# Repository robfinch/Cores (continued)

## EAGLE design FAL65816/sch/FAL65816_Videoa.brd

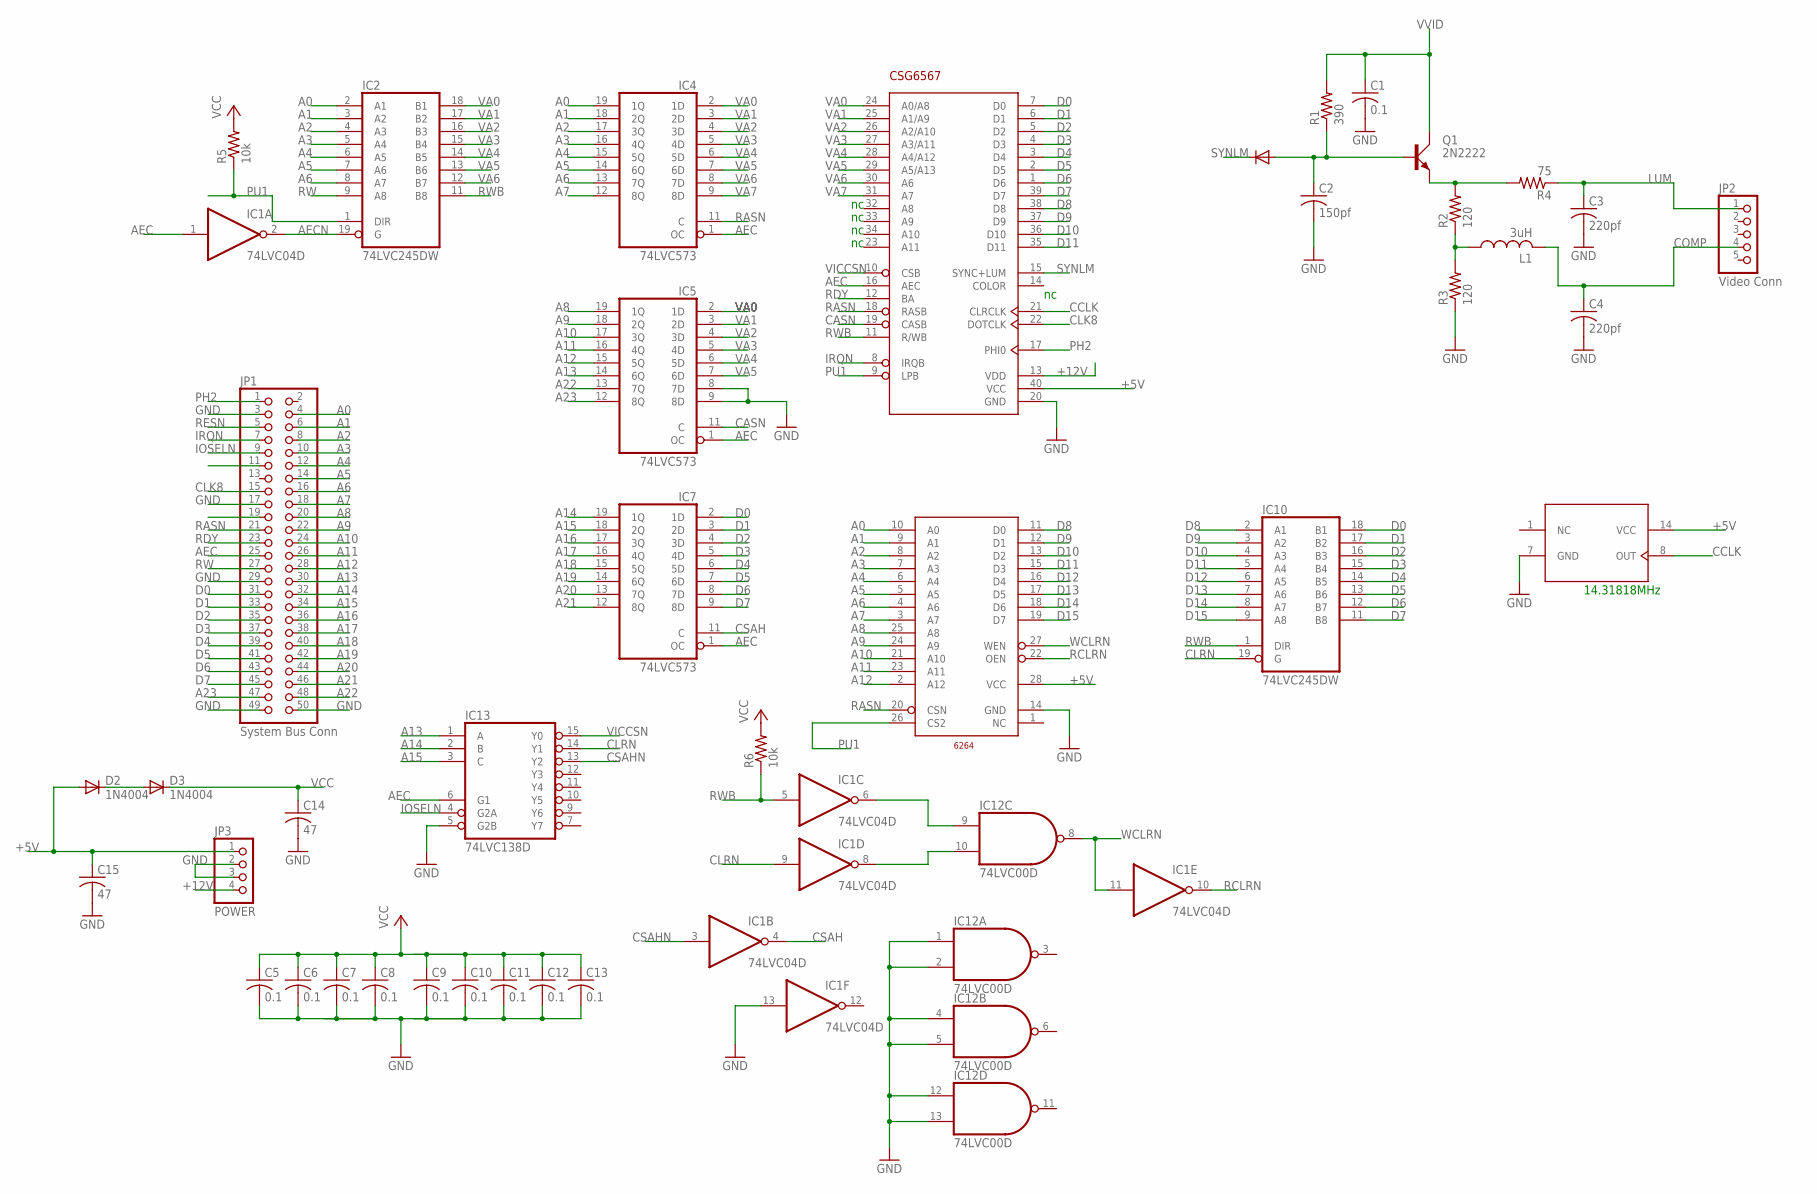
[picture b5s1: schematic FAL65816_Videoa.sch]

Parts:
C1, C5, C6, C7, C8, C9, C10, C11, C12, C13: 0.1; C050-024X044
C2: 150pf; C050-024X044
C3, C4: 220pf; C050-024X044
C14, C15: 47; C050-024X044
D2, D3: 1N4004; DO41-10
IC1: 74LVC04D; SO14
IC2, IC10: 74LVC245DW; SO20W
IC4, IC5, IC7: 74LVC573; SO20W
IC12: 74LVC00D; SO14
IC13: 74LVC138D; SO16
JP1: System Bus Conn; 2X25/90
JP2: Video Conn; 1X05
JP3: POWER; 1X04/90
L1: 3uH; 0204/7
Q1: 2N2222; TO18A
R1: 390; 0204/7
R2, R3: 120; 0204/7
R4: 75; 0204/7
R5, R6: 10k; 0204/7
U$1: CSG6567; DIP-40
U$3: OSC14; DIL14
U$4: 6264; DIL28-6

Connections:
+5V: C15.1, D2.A, JP3.1, U$1.40 (VCC), U$3.14 (VCC), U$4.28 (VCC)
+12V: JP3.4, U$1.13 (VDD)
A0: IC2.2 (A1), IC4.19 (1Q), JP1.4, U$4.10 (A0)
A1: IC2.3 (A2), IC4.18 (2Q), JP1.6, U$4.9 (A1)
A2: IC2.4 (A3), IC4.17 (3Q), JP1.8, U$4.8 (A2)
A3: IC2.5 (A4), IC4.16 (4Q), JP1.10, U$4.7 (A3)
A4: IC2.6 (A5), IC4.15 (5Q), JP1.12, U$4.6 (A4)
A5: IC2.7 (A6), IC4.14 (6Q), JP1.14, U$4.5 (A5)
A6: IC2.8 (A7), IC4.13 (7Q), JP1.16, U$4.4 (A6)
A7: IC4.12 (8Q), JP1.18, U$4.3 (A7)
A8: IC5.19 (1Q), JP1.20, U$4.25 (A8)
A9: IC5.18 (2Q), JP1.22, U$4.24 (A9)
A10: IC5.17 (3Q), JP1.24, U$4.21 (A10)
A11: IC5.16 (4Q), JP1.26, U$4.23 (A11)
A12: IC5.15 (5Q), JP1.28, U$4.2 (A12)
A13: IC5.14 (6Q), IC13.1 (A), JP1.30
A14: IC7.19 (1Q), IC13.2 (B), JP1.32
A15: IC7.18 (2Q), IC13.3 (C), JP1.34
A16: IC7.17 (3Q), JP1.36
A17: IC7.16 (4Q), JP1.38
A18: IC7.15 (5Q), JP1.40
A19: IC7.14 (6Q), JP1.42
A20: IC7.13 (7Q), JP1.44
A21: IC7.12 (8Q), JP1.46
A22: IC5.13 (7Q), JP1.48
A23: IC5.12 (8Q), JP1.47
AEC: IC1.1 (I), IC4.1 (OC), IC5.1 (OC), IC7.1 (OC), IC13.6 (G1), JP1.25, U$1.16 (AEC)
AECN: IC1.2 (O), IC2.19 (G)
CASN: IC5.11 (C), U$1.19 (CASB)
CCLK: U$1.21 (CLRCLK), U$3.8 (OUT)
CLK8: JP1.15, U$1.22 (DOTCLK)
CLRN: IC1.9 (I), IC10.19 (G), IC13.14 (Y1)
COMP: C4.1, JP2.4, L1.2
CSAH: IC1.4 (O), IC7.11 (C)
CSAHN: IC1.3 (I), IC13.13 (Y2)
D0: IC7.2 (1D), IC10.18 (B1), JP1.31, U$1.7 (D0)
D1: IC7.3 (2D), IC10.17 (B2), JP1.33, U$1.6 (D1)
D2: IC7.4 (3D), IC10.16 (B3), JP1.35, U$1.5 (D2)
D3: IC7.5 (4D), IC10.15 (B4), JP1.37, U$1.4 (D3)
D4: IC7.6 (5D), IC10.14 (B5), JP1.39, U$1.3 (D4)
D5: IC7.7 (6D), IC10.13 (B6), JP1.41, U$1.2 (D5)
D6: IC7.8 (7D), IC10.12 (B7), JP1.43, U$1.1 (D6)
D7: IC7.9 (8D), IC10.11 (B8), JP1.45, U$1.39 (D7)
D8: IC10.2 (A1), U$1.38 (D8), U$4.11 (D0)
D9: IC10.3 (A2), U$1.37 (D9), U$4.12 (D1)
D10: IC10.4 (A3), U$1.36 (D10), U$4.13 (D2)
D11: IC10.5 (A4), U$1.35 (D11), U$4.15 (D3)
D12: IC10.6 (A5), U$4.16 (D4)
D13: IC10.7 (A6), U$4.17 (D5)
D14: IC10.8 (A7), U$4.18 (D6)
D15: IC10.9 (A8), U$4.19 (D7)
GND: C1.2, C2.2, C3.2, C4.2, C5.2, C6.2, C7.2, C8.2, C9.2, C10.2, C11.2, C12.2, C13.2, C14.2, C15.2, IC1.7 (GND), IC1.13 (I), IC2.10 (GND), IC4.10 (GND), IC5.8 (7D), IC5.9 (8D), IC5.10 (GND), IC7.10 (GND), IC10.10 (GND), IC12.1 (I0), IC12.2 (I1), IC12.4 (I0), IC12.5 (I1), IC12.7 (GND), IC12.12 (I0), IC12.13 (I1), IC13.5 (G2B), IC13.8 (GND), JP1.3, JP1.17, JP1.29, JP1.49, JP1.50, JP3.2, JP3.3, R3.1, U$1.20 (GND), U$3.7 (GND), U$4.14 (GND)
IOSELN: IC13.4 (G2A), JP1.9
IRQN: JP1.7, U$1.8 (IRQB)
LUM: C3.1, JP2.1, R4.1
unnamed: D2.C, D3.A
unnamed: IC1.6 (O), IC12.9 (I0)
unnamed: IC1.8 (O), IC12.10 (I1)
unnamed: C2.1, Q1.B, R1.1
unnamed: L1.1, R2.1, R3.2
unnamed: Q1.E, R2.2, R4.2
PH2: JP1.1, U$1.17 (PHI0)
PU1: IC2.1 (DIR), R5.1, U$1.9 (LPB), U$4.26 (CS2)
RASN: IC4.11 (C), JP1.21, U$1.18 (RASB), U$4.20 (CSN)
RCLRN: IC1.10 (O), U$4.22 (OEN)
RDY: JP1.23, U$1.12 (BA)
RESN: JP1.5
RW: IC2.9 (A8), JP1.27
RWB: IC1.5 (I), IC2.11 (B8), IC10.1 (DIR), R6.1, U$1.11 (R/WB)
SYNLM: U$1.15 (SYNC+LUM)
VA0: IC2.18 (B1), IC4.2 (1D), IC5.2 (1D), U$1.24 (A0/A8)
VA1: IC2.17 (B2), IC4.3 (2D), IC5.3 (2D), U$1.25 (A1/A9)
VA2: IC2.16 (B3), IC4.4 (3D), IC5.4 (3D), U$1.26 (A2/A10)
VA3: IC2.15 (B4), IC4.5 (4D), IC5.5 (4D), U$1.27 (A3/A11)
VA4: IC2.14 (B5), IC4.6 (5D), IC5.6 (5D), U$1.28 (A4/A12)
VA5: IC2.13 (B6), IC4.7 (6D), IC5.7 (6D), U$1.29 (A5/A13)
VA6: IC2.12 (B7), IC4.8 (7D), U$1.30 (A6)
VA7: IC4.9 (8D), U$1.31 (A7)
VCC: C5.1, C6.1, C7.1, C8.1, C9.1, C10.1, C11.1, C12.1, C13.1, C14.1, D3.C, IC1.14 (VCC), IC2.20 (VCC), IC4.20 (VCC), IC5.20 (VCC), IC7.20 (VCC), IC10.20 (VCC), IC12.14 (VCC), IC13.16 (VCC), R5.2, R6.2
VICCSN: IC13.15 (Y0), U$1.10 (CSB)
VVID: C1.1, Q1.C, R1.2
WCLRN: IC1.11 (I), IC12.8 (O), U$4.27 (WEN)

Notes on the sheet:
14.31818MHz

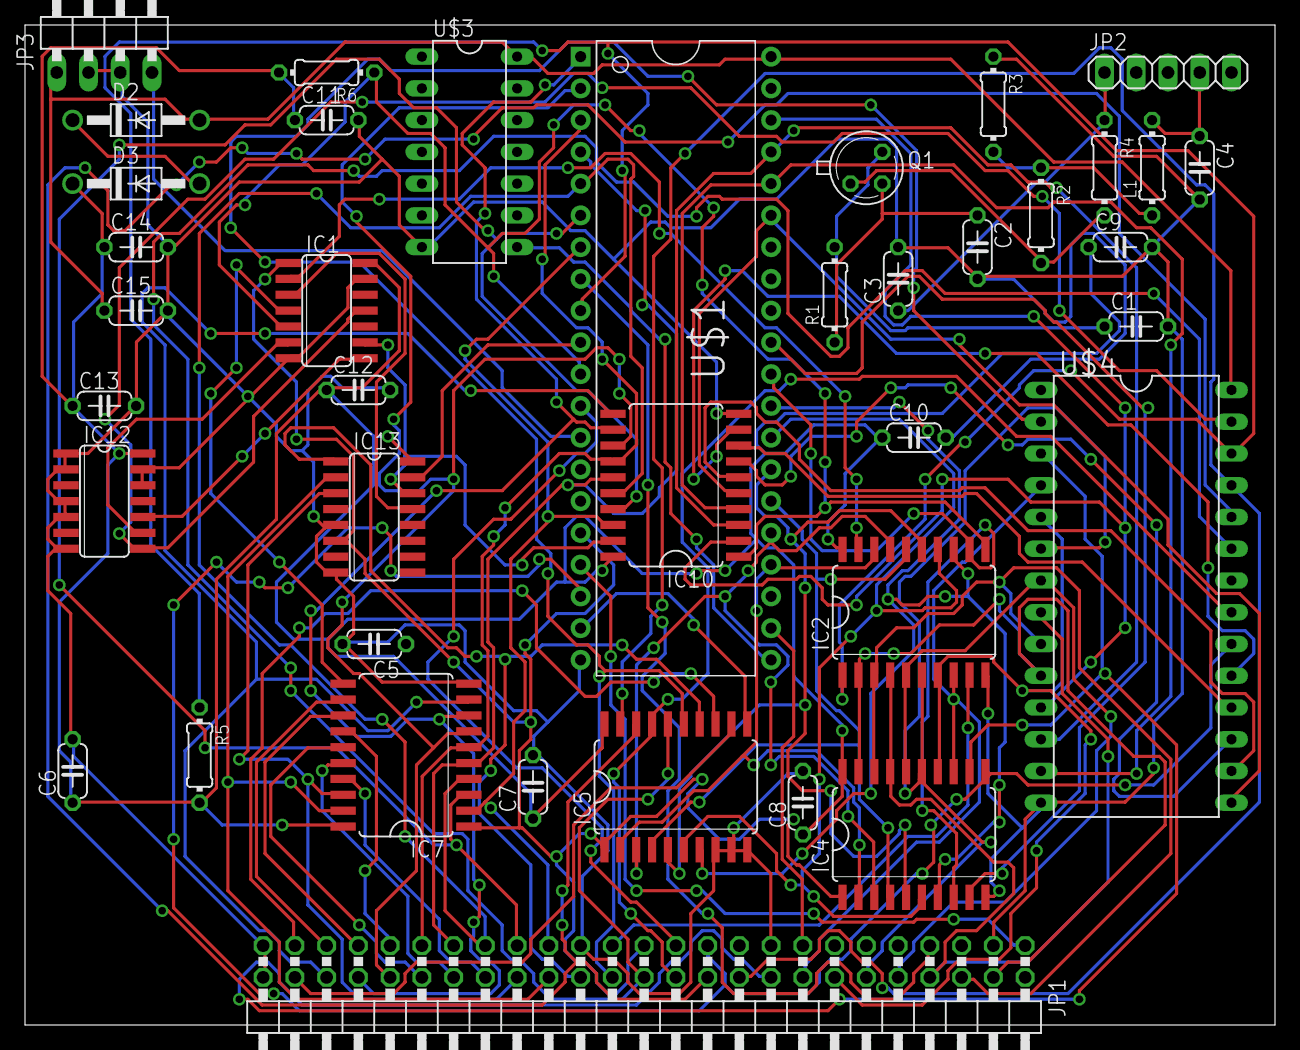
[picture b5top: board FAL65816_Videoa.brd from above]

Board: 2 copper layers, 100.0 x 80.0 mm, 39 parts (0 on the bottom side), 80 nets.

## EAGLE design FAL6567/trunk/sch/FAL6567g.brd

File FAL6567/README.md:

# FAL6567

This set of cores makes up a 6567 VIC-II compatible circuit. The core would be implmented in an FPGA or other PLD and would need additional logic for level translations to substitute into a 6567 socket.

## Features
HDMI output
16 sprites
80 column text mode

## Output
Most modern TV's and monitors support HDMI inputs.

## Sprites
By making use of fast paged mode, FPM, of the dynamic RAM, FAL6567 may support up to 16 sprites.
The additional sprites reuse the existing registers. There is a switch in register 32h which selects which sprite registers are visible.
Register 32h may be used to select legacy sprite operation and the set of sprite registers visible.
When 80 column text mode is active sprites may be positioned at only every other X pixel location. This is a design choice because there are 1040 horizontal positions in 80 column mode requiring 10 bits to represent, but the VIC-II register set has room for only a nine-bit coordinate.

## 80 Column Text
A modern display can easily display 80 columns of text in a crisp clean fashion without blurring or fuzziness.
Because the displayed image is rendered to an internal buffer to convert the image to DVI/HDMI output an 80 column mode is possible without needing to increase the frequency of memory access.
Twice as much memory is scanned for character data, this results in longer badlines.

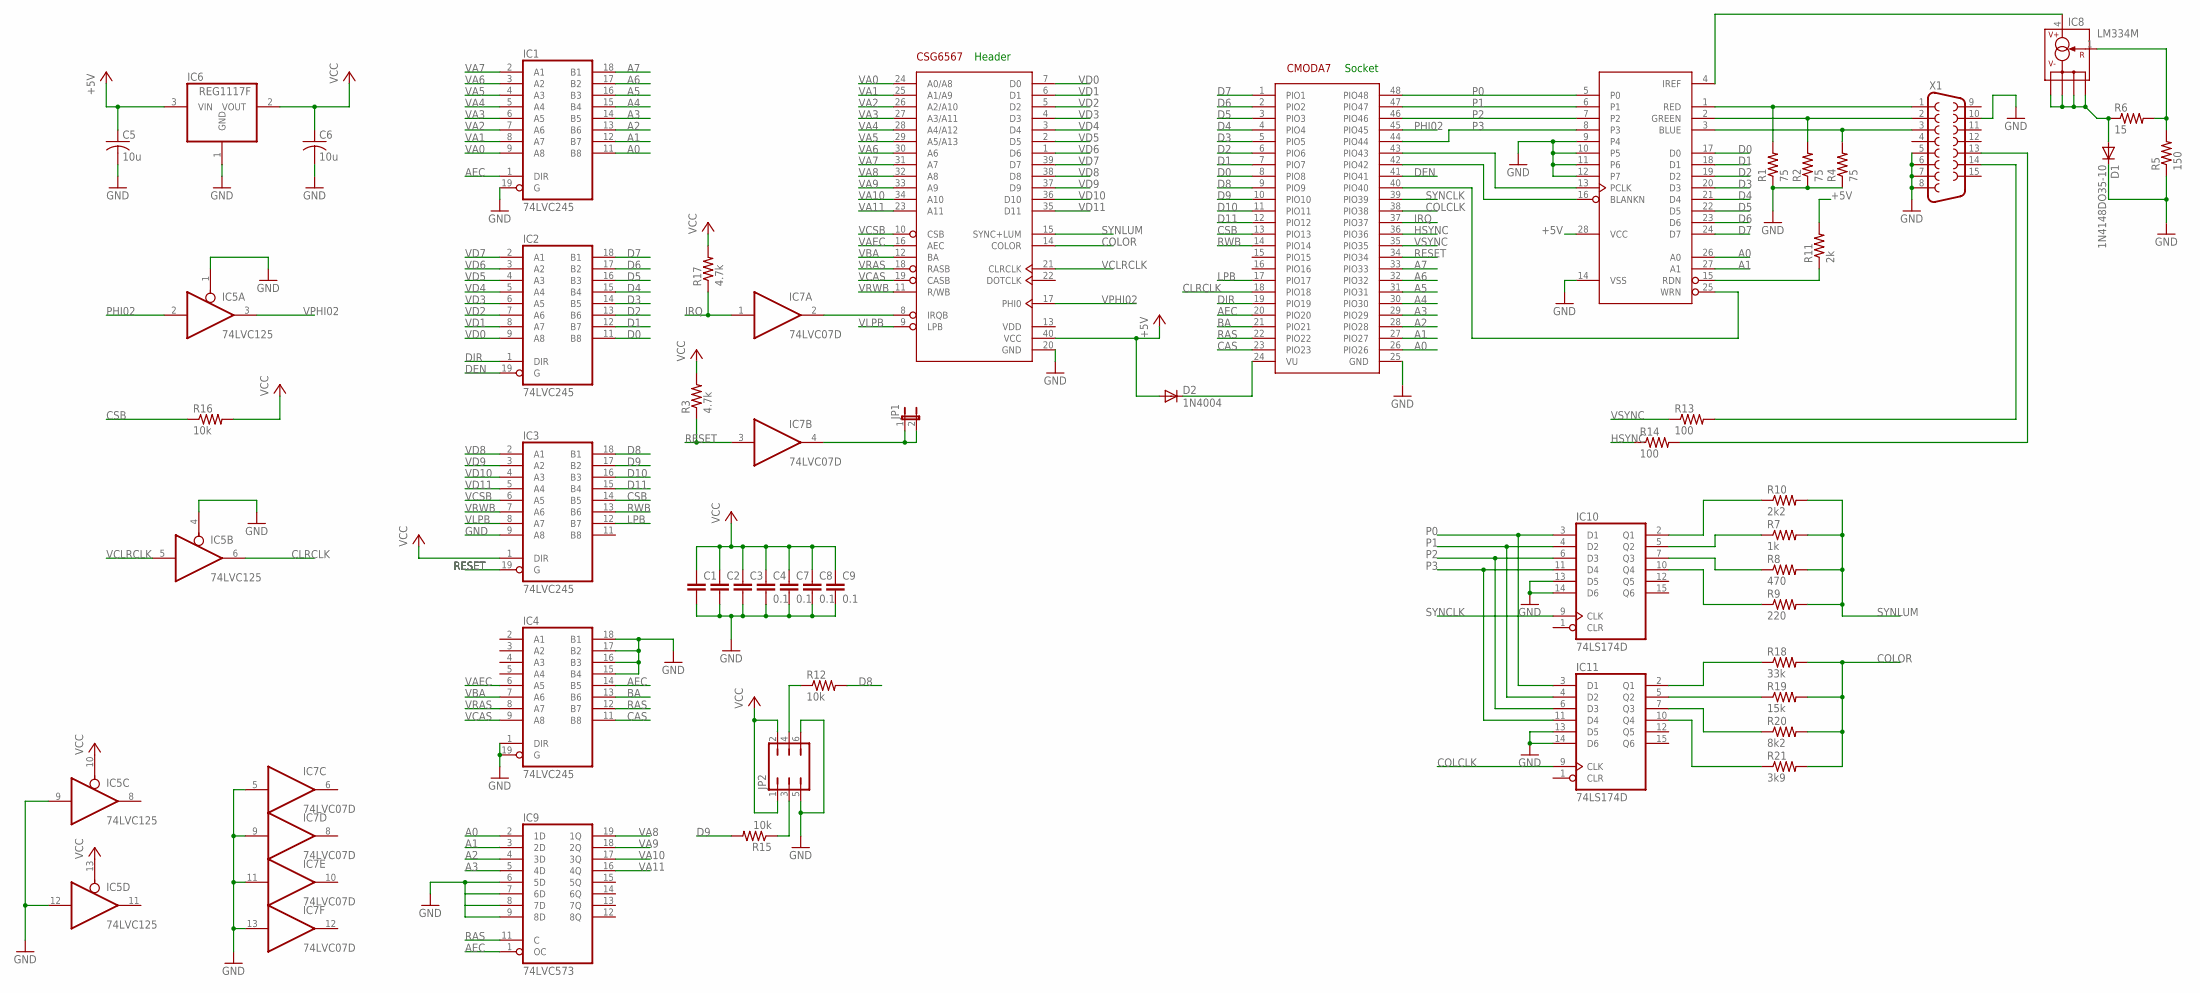
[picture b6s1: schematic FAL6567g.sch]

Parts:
C1, C2, C3: C-EU050-024X044; C050-024X044
C4, C7, C8, C9: 0.1; C050-024X044
C5, C6: 10u; C1206
D1: 1N4148DO35-10; DO35-10
D2: 1N4004; DO41-10
IC1, IC2, IC3, IC4: 74LVC245; SO20W
IC5: 74LVC125; SO14
IC6: REG1117F; DD-3
IC7: 74LVC07D; SO14
IC8: LM334M; SO08
IC9: 74LVC573; SO20W
IC10, IC11: 74LS174D; SO16
JP1: JP1E; JP1
JP2: JP3Q
R1, R2, R4: 75; 0204/7
R3, R17: 4.7k; 0204/7
R5: 150; 0204/7
R6: 15; 0204/7
R7: 1k; 0204/7
R8: 470; 0204/7
R9: 220; 0204/7
R10: 2k2; 0204/7
R11: 2k; 0204/7
R12, R15, R16: 10k; 0204/7
R13, R14: 100; 0204/7
R18: 33k; 0204/7
R19: 15k; 0204/7
R20: 8k2; 0204/7
R21: 3k9; 0204/7
U$1: CSG6567; DIP-40
U$2: CMODA7; DIL48
U$3: ADV476; DIL28-6
X1: F15HDV; HDF15V

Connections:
+5V: C5.1, D2.A, IC6.3 (VIN), R11.2, U$1.40 (VCC), U$3.28 (VCC)
A0: IC1.11 (B8), IC9.2 (1D), U$2.26 (PIO26), U$3.26 (A0)
A1: IC1.12 (B7), IC9.3 (2D), U$2.27 (PIO27), U$3.27 (A1)
A2: IC1.13 (B6), IC9.4 (3D), U$2.28 (PIO28)
A3: IC1.14 (B5), IC9.5 (4D), U$2.29 (PIO29)
A4: IC1.15 (B4), U$2.30 (PIO30)
A5: IC1.16 (B3), U$2.31 (PIO31)
A6: IC1.17 (B2), U$2.32 (PIO32)
A7: IC1.18 (B1), U$2.33 (PIO33)
AEC: IC1.1 (DIR), IC4.14 (B5), IC9.1 (OC), U$2.20 (PIO20)
BA: IC4.13 (B6), U$2.21 (PIO21)
CAS: IC4.11 (B8), U$2.23 (PIO23)
CLRCLK: IC5.6 (O), U$2.18 (PIO18)
COLCLK: IC11.9 (CLK), U$2.38 (PIO38)
COLOR: R18.2, R19.2, R20.2, R21.2, U$1.14 (COLOR)
CSB: IC3.14 (B5), R16.1, U$2.13 (PIO13)
D0: IC2.11 (B8), U$2.8 (PIO8), U$3.17 (D0)
D1: IC2.12 (B7), U$2.7 (PIO7), U$3.18 (D1)
D2: IC2.13 (B6), U$2.6 (PIO6), U$3.19 (D2)
D3: IC2.14 (B5), U$2.5 (PIO5), U$3.20 (D3)
D4: IC2.15 (B4), U$2.4 (PIO4), U$3.21 (D4)
D5: IC2.16 (B3), U$2.3 (PIO3), U$3.22 (D5)
D6: IC2.17 (B2), U$2.2 (PIO2), U$3.23 (D6)
D7: IC2.18 (B1), U$2.1 (PIO1), U$3.24 (D7)
D8: IC3.18 (B1), R12.2, U$2.9 (PIO9)
D9: IC3.17 (B2), R15.2, U$2.10 (PIO10)
D10: IC3.16 (B3), U$2.11 (PIO11)
D11: IC3.15 (B4), U$2.12 (PIO12)
DEN: IC2.19 (G), U$2.41 (PIO41)
DIR: IC2.1 (DIR), U$2.19 (PIO19)
GND: C1.2, C2.2, C3.2, C4.2, C5.2, C6.2, C7.2, C8.2, C9.2, D1.C, IC1.10 (GND), IC1.19 (G), IC2.10 (GND), IC3.9 (A8), IC3.10 (GND), IC4.1 (DIR), IC4.10 (GND), IC4.15 (B4), IC4.16 (B3), IC4.17 (B2), IC4.18 (B1), IC4.19 (G), IC5.1 (OE), IC5.4 (OE), IC5.7 (GND), IC5.9 (I), IC5.12 (I), IC6.1 (GND), IC7.5 (I), IC7.7 (GND), IC7.9 (I), IC7.11 (I), IC7.13 (I), IC9.6 (5D), IC9.9 (8D), IC9.10 (GND), IC10.8 (GND), IC10.13 (D5), IC10.14 (D6), IC11.8 (GND), IC11.13 (D5), IC11.14 (D6), JP2.5, JP2.6, R1.1, R2.1, R4.1, R5.1, U$1.20 (GND), U$2.25 (GND), U$3.9 (P4), U$3.10 (P5), U$3.11 (P6), U$3.12 (P7), U$3.14 (VSS), X1.5, X1.6, X1.7, X1.8, X1.10
HSYNC: R14.1, U$2.36 (PIO36)
IRQ: IC7.1 (I), R17.1, U$2.37 (PIO37)
LPB: IC3.12 (B7), U$2.17 (PIO17)
MD0: JP2.4, R12.1
MD1: JP2.3, R15.1
unnamed: IC7.2 (O), U$1.8 (IRQB)
unnamed: IC10.2 (Q1), R10.1
unnamed: D2.C, U$2.24 (VU)
unnamed: IC10.5 (Q2), R7.1
unnamed: R1.2, U$3.1 (RED), X1.1
unnamed: IC7.4 (O), JP1.1, JP1.2
unnamed: IC10.7 (Q3), R8.1
unnamed: R2.2, U$3.2 (GREEN), X1.2
unnamed: IC10.10 (Q4), R9.1
unnamed: R14.2, X1.13
unnamed: R13.2, X1.14
unnamed: U$2.40 (PIO40), U$3.25 (WRN)
unnamed: R4.2, U$3.3 (BLUE), X1.3
unnamed: IC8.1 (R), R5.2, R6.2
unnamed: IC11.2 (Q1), R18.1
unnamed: IC11.5 (Q2), R19.1
unnamed: D1.A, IC8.2 (V-), IC8.3 (V-), IC8.6 (V-), IC8.7 (V-), R6.1
unnamed: IC8.4 (V+), U$3.4 (IREF)
unnamed: IC11.7 (Q3), R20.1
unnamed: U$2.43 (PIO43), U$3.13 (PCLK)
unnamed: U$2.42 (PIO42), U$3.16 (BLANKN)
unnamed: IC11.10 (Q4), R21.1
unnamed: R11.1, U$3.15 (RDN)
P0: IC10.3 (D1), IC11.3 (D1), U$2.48 (PIO48), U$3.5 (P0)
P1: IC10.4 (D2), IC11.4 (D2), U$2.47 (PIO47), U$3.6 (P1)
P2: IC10.6 (D3), IC11.6 (D3), U$2.46 (PIO46), U$3.7 (P2)
P3: IC10.11 (D4), IC11.11 (D4), U$2.44 (PIO44), U$3.8 (P3)
PHI02: IC5.2 (I), U$2.45 (PIO45)
RAS: IC4.12 (B7), IC9.11 (C), U$2.22 (PIO22)
RESET: IC3.19 (G), IC7.3 (I), R3.1, U$2.34 (PIO34)
RWB: IC3.13 (B6), U$2.14 (PIO14)
SYNCLK: IC10.9 (CLK), U$2.39 (PIO39)
SYNLUM: R7.2, R8.2, R9.2, R10.2, U$1.15 (SYNC+LUM)
VA0: IC1.9 (A8), U$1.24 (A0/A8)
VA1: IC1.8 (A7), U$1.25 (A1/A9)
VA2: IC1.7 (A6), U$1.26 (A2/A10)
VA3: IC1.6 (A5), U$1.27 (A3/A11)
VA4: IC1.5 (A4), U$1.28 (A4/A12)
VA5: IC1.4 (A3), U$1.29 (A5/A13)
VA6: IC1.3 (A2), U$1.30 (A6)
VA7: IC1.2 (A1), U$1.31 (A7)
VA8: IC9.19 (1Q), U$1.32 (A8)
VA9: IC9.18 (2Q), U$1.33 (A9)
VA10: IC9.17 (3Q), U$1.34 (A10)
VA11: IC9.16 (4Q), U$1.23 (A11)
VAEC: IC4.6 (A5), U$1.16 (AEC)
VBA: IC4.7 (A6), U$1.12 (BA)
VCAS: IC4.9 (A8), U$1.19 (CASB)
VCC: C1.1, C2.1, C3.1, C4.1, C6.1, C7.1, C8.1, C9.1, IC1.20 (VCC), IC2.20 (VCC), IC3.1 (DIR), IC3.20 (VCC), IC4.20 (VCC), IC5.10 (OE), IC5.13 (OE), IC5.14 (VCC), IC6.2 (VOUT), IC7.14 (VCC), IC9.20 (VCC), IC10.16 (VCC), IC11.16 (VCC), JP2.1, JP2.2, R3.2, R16.2, R17.2
VCLRCLK: IC5.5 (I), U$1.21 (CLRCLK)
VCSB: IC3.6 (A5), U$1.10 (CSB)
VD0: IC2.9 (A8), U$1.7 (D0)
VD1: IC2.8 (A7), U$1.6 (D1)
VD2: IC2.7 (A6), U$1.5 (D2)
VD3: IC2.6 (A5), U$1.4 (D3)
VD4: IC2.5 (A4), U$1.3 (D4)
VD5: IC2.4 (A3), U$1.2 (D5)
VD6: IC2.3 (A2), U$1.1 (D6)
VD7: IC2.2 (A1), U$1.39 (D7)
VD8: IC3.2 (A1), U$1.38 (D8)
VD9: IC3.3 (A2), U$1.37 (D9)
VD10: IC3.4 (A3), U$1.36 (D10)
VD11: IC3.5 (A4), U$1.35 (D11)
VDD: U$1.13 (VDD)
VLPB: IC3.8 (A7), U$1.9 (LPB)
VPHI02: IC5.3 (O), U$1.17 (PHI0)
VRAS: IC4.8 (A7), U$1.18 (RASB)
VRWB: IC3.7 (A6), U$1.11 (R/WB)
VSYNC: R13.1, U$2.35 (PIO35)

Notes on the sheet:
Header
Socket

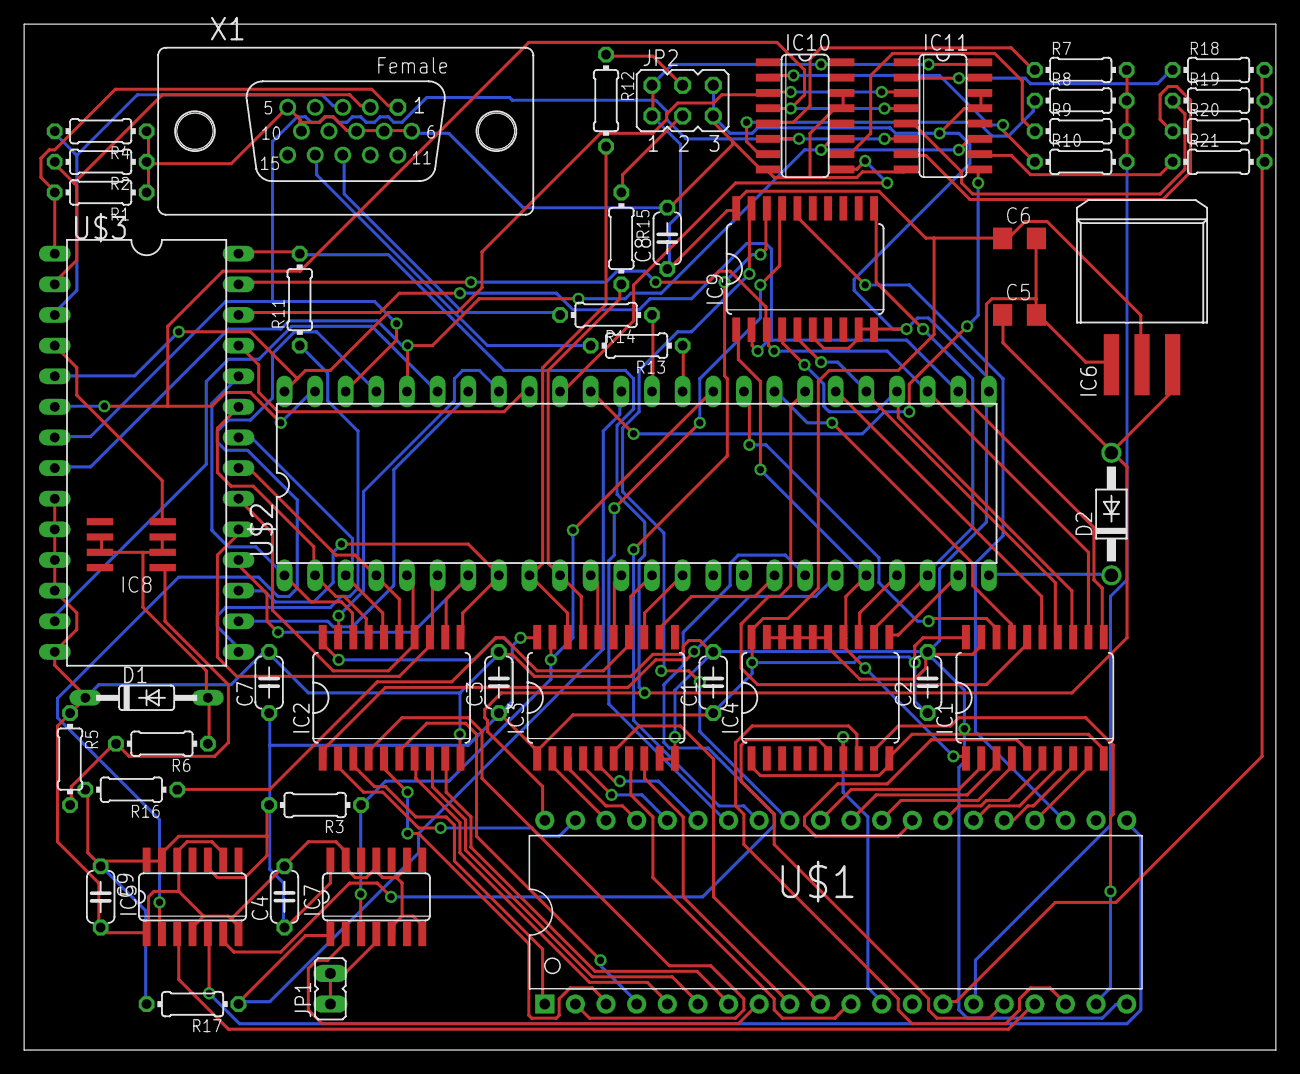
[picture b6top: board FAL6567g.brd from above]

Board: 2 copper layers, 103.8 x 85.1 mm, 50 parts (0 on the bottom side), 104 nets.

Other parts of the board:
DRILEGEND: DRILEGEND

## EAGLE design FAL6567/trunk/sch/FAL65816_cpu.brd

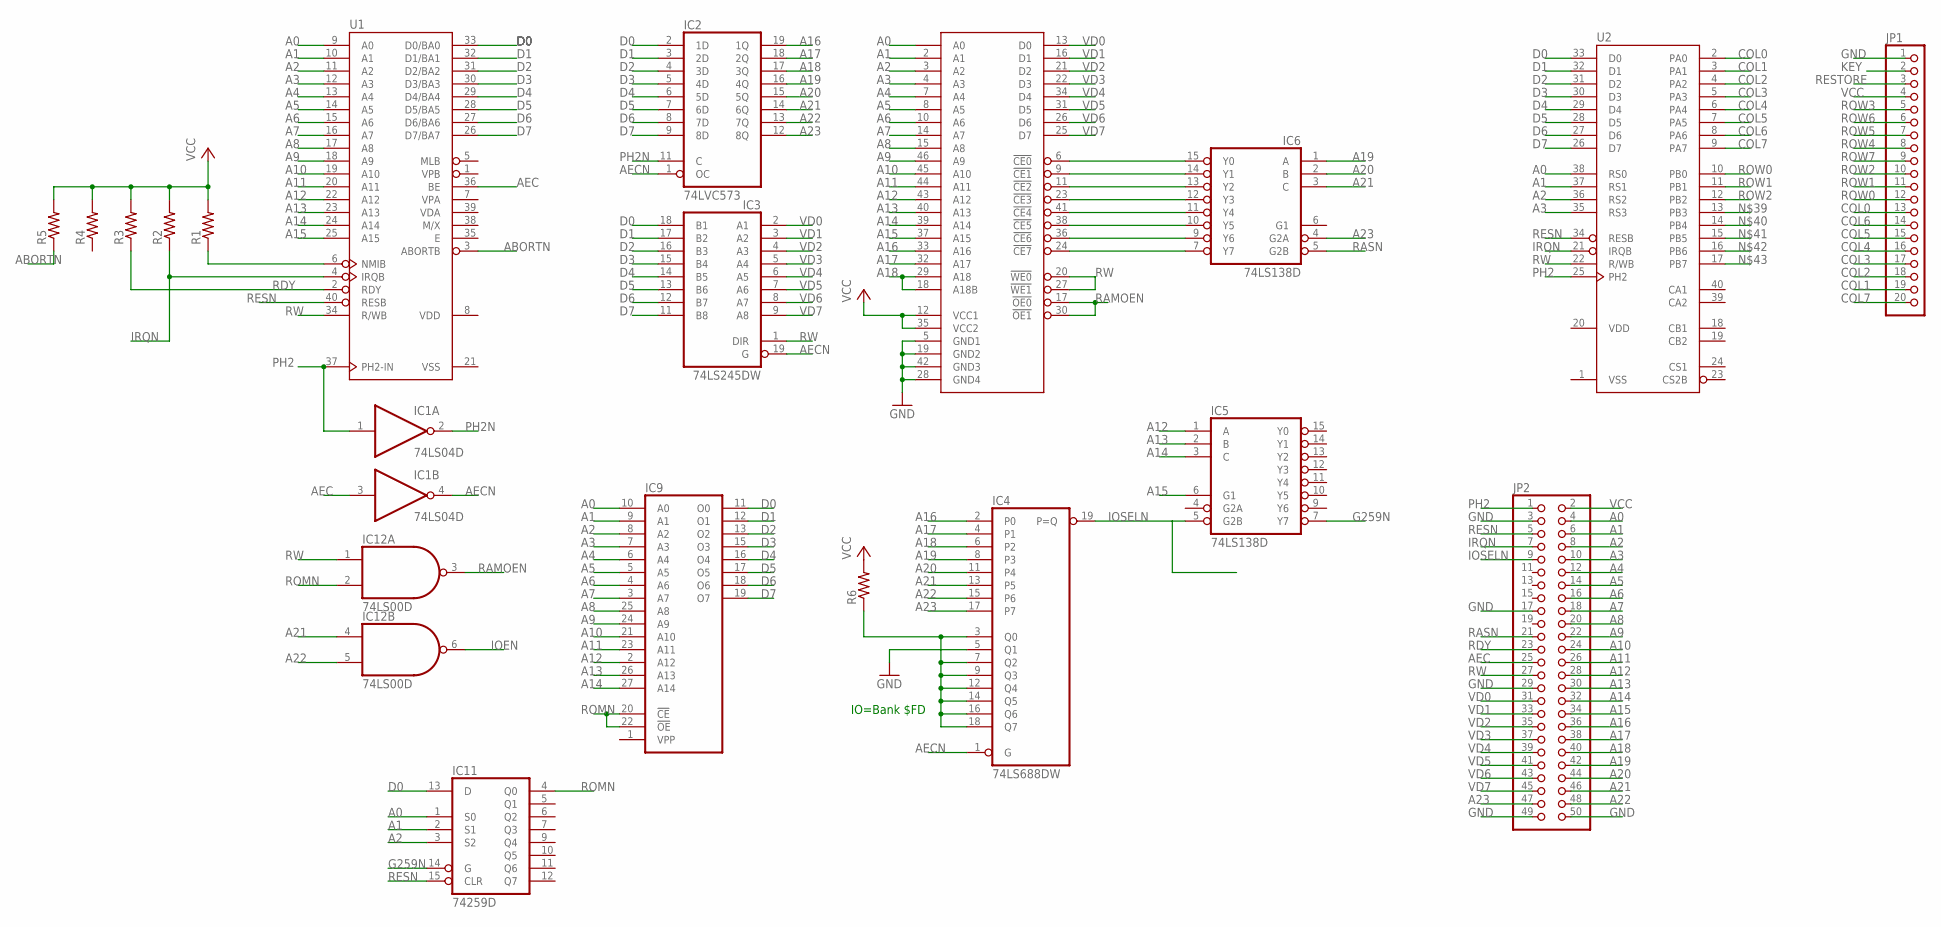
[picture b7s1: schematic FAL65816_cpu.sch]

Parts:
IC1: 74LS04D; SO14
IC2: 74LVC573; SO20W
IC3: 74LS245DW; SO20W
IC4: 74LS688DW; SO20W
IC5, IC6: 74LS138D; SO16
IC9: 27256; DIL28
IC11: 74259D; SO16
IC12: 74LS00D; SO14
JP1: PINHD-1X20; 1X20
JP2: PINHD-2X25; 2X25
R1, R2, R3, R4, R5: R-US_0207/10; 0207/10
R6: R-US_0204/7; 0204/7
U1: W65C816SP; DIP-40
U2: G65SC22P; DIP-40
U$2: WM-1RAM; DIL46-1

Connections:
A0: IC9.10 (A0), IC11.1 (S0), JP2.4, U1.9 (A0), U2.38 (RS0), U$2.1 (A0)
A1: IC9.9 (A1), IC11.2 (S1), JP2.6, U1.10 (A1), U2.37 (RS1), U$2.2 (A1)
A2: IC9.8 (A2), IC11.3 (S2), JP2.8, U1.11 (A2), U2.36 (RS2), U$2.3 (A2)
A3: IC9.7 (A3), JP2.10, U1.12 (A3), U2.35 (RS3), U$2.4 (A3)
A4: IC9.6 (A4), JP2.12, U1.13 (A4), U$2.7 (A4)
A5: IC9.5 (A5), JP2.14, U1.14 (A5), U$2.8 (A5)
A6: IC9.4 (A6), JP2.16, U1.15 (A6), U$2.10 (A6)
A7: IC9.3 (A7), JP2.18, U1.16 (A7), U$2.14 (A7)
A8: IC9.25 (A8), JP2.20, U1.17 (A8), U$2.15 (A8)
A9: IC9.24 (A9), JP2.22, U1.18 (A9), U$2.46 (A9)
A10: IC9.21 (A10), JP2.24, U1.19 (A10), U$2.45 (A10)
A11: IC9.23 (A11), JP2.26, U1.20 (A11), U$2.44 (A11)
A12: IC5.1 (A), IC9.2 (A12), JP2.28, U1.22 (A12), U$2.43 (A12)
A13: IC5.2 (B), IC9.26 (A13), JP2.30, U1.23 (A13), U$2.40 (A13)
A14: IC5.3 (C), IC9.27 (A14), JP2.32, U1.24 (A14), U$2.39 (A14)
A15: IC5.6 (G1), JP2.34, U1.25 (A15), U$2.37 (A15)
A16: IC2.19 (1Q), IC4.2 (P0), JP2.36, U$2.33 (A16)
A17: IC2.18 (2Q), IC4.4 (P1), JP2.38, U$2.32 (A17)
A18: IC2.17 (3Q), IC4.6 (P2), JP2.40, U$2.18 (A18B), U$2.29 (A18)
A19: IC2.16 (4Q), IC4.8 (P3), IC6.1 (A), JP2.42
A20: IC2.15 (5Q), IC4.11 (P4), IC6.2 (B), JP2.44
A21: IC2.14 (6Q), IC4.13 (P5), IC6.3 (C), IC12.4 (I0), JP2.46
A22: IC2.13 (7Q), IC4.15 (P6), IC12.5 (I1), JP2.48
A23: IC2.12 (8Q), IC4.17 (P7), IC6.4 (G2A), JP2.47
ABORTN: R5.1, U1.3 (ABORTB)
AEC: IC1.3 (I), JP2.25, U1.36 (BE)
AECN: IC1.4 (O), IC2.1 (OC), IC3.19 (G), IC4.1 (G)
COL0: JP1.13, U2.2 (PA0)
COL1: JP1.19, U2.3 (PA1)
COL2: JP1.18, U2.4 (PA2)
COL3: JP1.17, U2.5 (PA3)
COL4: JP1.16, U2.6 (PA4)
COL5: JP1.15, U2.7 (PA5)
COL6: JP1.14, U2.8 (PA6)
COL7: JP1.20, U2.9 (PA7)
D0: IC2.2 (1D), IC3.18 (B1), IC9.11 (O0), IC11.13 (D), U1.33 (D0/BA0), U2.33 (D0)
D1: IC2.3 (2D), IC3.17 (B2), IC9.12 (O1), U1.32 (D1/BA1), U2.32 (D1)
D2: IC2.4 (3D), IC3.16 (B3), IC9.13 (O2), U1.31 (D2/BA2), U2.31 (D2)
D3: IC2.5 (4D), IC3.15 (B4), IC9.15 (O3), U1.30 (D3/BA3), U2.30 (D3)
D4: IC2.6 (5D), IC3.14 (B5), IC9.16 (O4), U1.29 (D4/BA4), U2.29 (D4)
D5: IC2.7 (6D), IC3.13 (B6), IC9.17 (O5), U1.28 (D5/BA5), U2.28 (D5)
D6: IC2.8 (7D), IC3.12 (B7), IC9.18 (O6), U1.27 (D6/BA6), U2.27 (D6)
D7: IC2.9 (8D), IC3.11 (B8), IC9.19 (O7), U1.26 (D7/BA7), U2.26 (D7)
G259N: IC5.7 (Y7), IC11.14 (G)
GND: IC1.7 (GND), IC2.10 (GND), IC3.10 (GND), IC4.5 (Q1), IC4.10 (GND), IC5.8 (GND), IC6.8 (GND), IC9.14 (GND), IC11.8 (GND), IC12.7 (GND), JP1.1, JP2.3, JP2.17, JP2.29, JP2.49, JP2.50, U$2.5 (GND1), U$2.19 (GND2), U$2.28 (GND4), U$2.42 (GND3)
IOEN: IC12.6 (O)
IOSELN: IC4.19 (P=Q), IC5.5 (G2B), JP2.9
IRQN: JP2.7, R2.1, U1.4 (IRQB), U2.21 (IRQB)
KEY: JP1.2
unnamed: R1.1, U1.6 (NMIB)
unnamed: IC6.15 (Y0), U$2.6 (!CE0)
unnamed: IC6.14 (Y1), U$2.9 (!CE1)
unnamed: IC6.13 (Y2), U$2.11 (!CE2)
unnamed: IC6.12 (Y3), U$2.23 (!CE3)
unnamed: IC6.11 (Y4), U$2.41 (!CE4)
unnamed: IC6.10 (Y5), U$2.38 (!CE5)
unnamed: IC6.9 (Y6), U$2.36 (!CE6)
unnamed: IC6.7 (Y7), U$2.24 (!CE7)
unnamed: IC4.3 (Q0), IC4.7 (Q2), IC4.9 (Q3), IC4.12 (Q4), IC4.14 (Q5), IC4.16 (Q6), IC4.18 (Q7), R6.1
PH2: IC1.1 (I), JP2.1, U1.37 (PH2-IN), U2.25 (PH2)
PH2N: IC1.2 (O), IC2.11 (C)
RAMOEN: IC12.3 (O), U$2.17 (!OE0), U$2.30 (!OE1)
RASN: IC6.5 (G2B), JP2.21
RDY: JP2.23, R3.1, U1.2 (RDY)
RESN: IC11.15 (CLR), JP2.5, U1.40 (RESB), U2.34 (RESB)
RESTORE: JP1.3
ROMN: IC9.20 (!CE), IC9.22 (!OE), IC11.4 (Q0), IC12.2 (I1)
ROW0: JP1.12, U2.10 (PB0)
ROW1: JP1.11, U2.11 (PB1)
ROW2: JP1.10, U2.12 (PB2)
ROW3: JP1.5
ROW4: JP1.8
ROW5: JP1.7
ROW6: JP1.6
ROW7: JP1.9
RW: IC3.1 (DIR), IC12.1 (I0), JP2.27, U1.34 (R/WB), U2.22 (R/WB), U$2.20 (!WE0), U$2.27 (!WE1)
VCC: IC1.14 (VCC), IC2.20 (VCC), IC3.20 (VCC), IC4.20 (VCC), IC5.16 (VCC), IC6.16 (VCC), IC9.28 (VCC), IC11.16 (VCC), IC12.14 (VCC), JP1.4, JP2.2, R1.2, R2.2, R3.2, R4.2, R5.2, R6.2, U$2.12 (VCC1), U$2.35 (VCC2)
VD0: IC3.2 (A1), JP2.31, U$2.13 (D0)
VD1: IC3.3 (A2), JP2.33, U$2.16 (D1)
VD2: IC3.4 (A3), JP2.35, U$2.21 (D2)
VD3: IC3.5 (A4), JP2.37, U$2.22 (D3)
VD4: IC3.6 (A5), JP2.39, U$2.34 (D4)
VD5: IC3.7 (A6), JP2.41, U$2.31 (D5)
VD6: IC3.8 (A7), JP2.43, U$2.26 (D6)
VD7: IC3.9 (A8), JP2.45, U$2.25 (D7)
VDD: U1.8 (VDD), U2.20 (VDD)

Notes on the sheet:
IO=Bank $FD

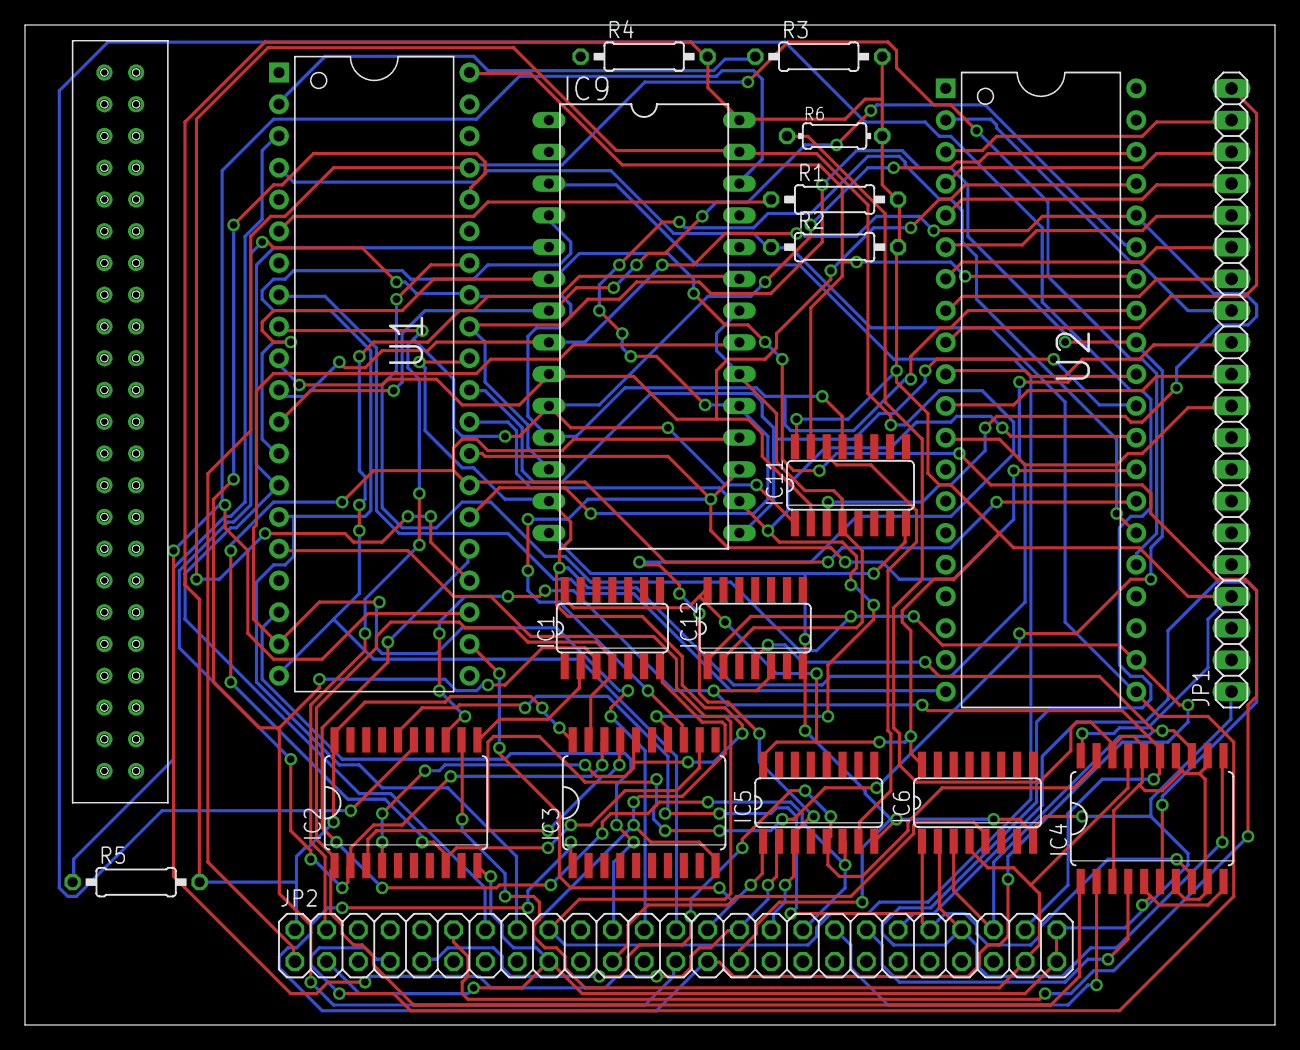
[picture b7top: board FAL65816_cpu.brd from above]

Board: 2 copper layers, 100.0 x 80.0 mm, 20 parts (0 on the bottom side), 78 nets.

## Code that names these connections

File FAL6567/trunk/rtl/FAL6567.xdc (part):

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#set_property -dict { PACKAGE_PIN M1    IOSTANDARD LVCMOS33 } [get_ports { pio2[0] }]; #IO_L9N_T1_DQS_AD7N_35 Sch=pio[17]
#set_property -dict { PACKAGE_PIN N3    IOSTANDARD LVCMOS33 } [get_ports { pio2[1] }]; #IO_L12P_T1_MRCC_35 Sch=pio[18]
set_property -dict { PACKAGE_PIN P3    IOSTANDARD LVCMOS33 } [get_ports { dir }]; #IO_L12N_T1_MRCC_35 Sch=pio[19]
set_property -dict { PACKAGE_PIN M2    IOSTANDARD LVCMOS33 } [get_ports { aec }]; #IO_L9P_T1_DQS_AD7P_35 Sch=pio[20]
set_property -dict { PACKAGE_PIN N1    IOSTANDARD LVCMOS33 } [get_ports { ba }]; #IO_L10N_T1_AD15N_35 Sch=pio[21]
set_property -dict { PACKAGE_PIN N2    IOSTANDARD LVCMOS33 } [get_ports { ras_n }]; #IO_L10P_T1_AD15P_35 Sch=pio[22]
set_property -dict { PACKAGE_PIN P1    IOSTANDARD LVCMOS33 } [get_ports { cas_n }]; #IO_L19N_T3_VREF_35 Sch=pio[23]
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set_property -dict { PACKAGE_PIN V2    IOSTANDARD TMDS_33 } [get_ports { TMDS_OUT_data_p[2] }]; #IO_L5P_T0_34 Sch=pio[33]
set_property -dict { PACKAGE_PIN W2    IOSTANDARD TMDS_33 } [get_ports { TMDS_OUT_data_n[2] }]; #IO_L5N_T0_34 Sch=pio[32]
set_property -dict { PACKAGE_PIN W3    IOSTANDARD LVCMOS33 } [get_ports { RESET }]; #IO_L6N_T0_VREF_34 Sch=pio[34]
set_property -dict { PACKAGE_PIN V3    IOSTANDARD LVCMOS33 } [get_ports { phi02 }]; #IO_L6P_T0_34 Sch=pio[35]
#set_property -dict { PACKAGE_PIN W5    IOSTANDARD LVCMOS33 } [get_ports { pio3[10] }]; #IO_L12P_T1_MRCC_34 Sch=pio[36]
set_property -dict { PACKAGE_PIN V4    IOSTANDARD LVCMOS33 } [get_ports { irq }]; #IO_L11N_T1_SRCC_34 Sch=pio[37]
#set_property -dict { PACKAGE_PIN U4    IOSTANDARD LVCMOS33 } [get_ports { pio3[12] }]; #IO_L11P_T1_SRCC_34 Sch=pio[38]
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#set_property -dict { PACKAGE_PIN V13   IOSTANDARD LVCMOS33 } [get_ports { MemDB[5]   }]; #IO_L24P_T3_A01_D17_14 Sch=sram-dq[5]
#set_property -dict { PACKAGE_PIN V14   IOSTANDARD LVCMOS33 } [get_ports { MemDB[6]   }]; #IO_L24N_T3_A00_D16_14 Sch=sram-dq[6]
#set_property -dict { PACKAGE_PIN U14   IOSTANDARD LVCMOS33 } [get_ports { MemDB[7]   }]; #IO_25_14 Sch=sram-dq[7]
#set_property -dict { PACKAGE_PIN P19   IOSTANDARD LVCMOS33 } [get_ports { RamOEn     }]; #IO_L10P_T1_D14_14 Sch=sram-oe
#set_property -dict { PACKAGE_PIN R19   IOSTANDARD LVCMOS33 } [get_ports { RamWEn     }]; #IO_L10N_T1_D15_14 Sch=sram-we
#set_property -dict { PACKAGE_PIN N19   IOSTANDARD LVCMOS33 } [get_ports { RamCEn     }]; #IO_L9N_T1_DQS_D13_14 Sch=sram-ce
#set_output_delay -clock [ get_clocks clk120_cs02clkgen ] -max 2.0 [get_ports {MemAdr[*]} ]
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
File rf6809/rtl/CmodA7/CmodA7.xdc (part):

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#set_property -dict { PACKAGE_PIN J3    IOSTANDARD LVCMOS33 } [get_ports { blue[1] }]; #IO_L7P_T1_AD6P_35 Sch=pio[10]
#set_property -dict { PACKAGE_PIN J1    IOSTANDARD LVCMOS33 } [get_ports { blue[2] }]; #IO_L3N_T0_DQS_AD5N_35 Sch=pio[11]
#set_property -dict { PACKAGE_PIN K2    IOSTANDARD LVCMOS33 } [get_ports { blue[3] }]; #IO_L5P_T0_AD13P_35 Sch=pio[12]
#set_property -dict { PACKAGE_PIN L1    IOSTANDARD LVCMOS33 } [get_ports { hsync }]; #IO_L6N_T0_VREF_35 Sch=pio[13]
#set_property -dict { PACKAGE_PIN L2    IOSTANDARD LVCMOS33 } [get_ports { vsync }]; #IO_L5N_T0_AD13N_35 Sch=pio[14]

set_property -dict { PACKAGE_PIN M1    IOSTANDARD LVCMOS33 } [get_ports { pio2[0] }]; #IO_L9N_T1_DQS_AD7N_35 Sch=pio[17]
set_property -dict { PACKAGE_PIN N3    IOSTANDARD LVCMOS33 } [get_ports { pio2[1] }]; #IO_L12P_T1_MRCC_35 Sch=pio[18]
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set_property -dict { PACKAGE_PIN V13   IOSTANDARD LVCMOS33 } [get_ports { MemDB[5]   }]; #IO_L24P_T3_A01_D17_14 Sch=sram-dq[5]
set_property -dict { PACKAGE_PIN V14   IOSTANDARD LVCMOS33 } [get_ports { MemDB[6]   }]; #IO_L24N_T3_A00_D16_14 Sch=sram-dq[6]
set_property -dict { PACKAGE_PIN U14   IOSTANDARD LVCMOS33 } [get_ports { MemDB[7]   }]; #IO_25_14 Sch=sram-dq[7]
set_property -dict { PACKAGE_PIN P19   IOSTANDARD LVCMOS33 } [get_ports { RamOEn     }]; #IO_L10P_T1_D14_14 Sch=sram-oe
set_property -dict { PACKAGE_PIN R19   IOSTANDARD LVCMOS33 } [get_ports { RamWEn     }]; #IO_L10N_T1_D15_14 Sch=sram-we
set_property -dict { PACKAGE_PIN N19   IOSTANDARD LVCMOS33 } [get_ports { RamCEn     }]; #IO_L9N_T1_DQS_D13_14 Sch=sram-ce
set_output_delay -clock [ get_clocks clk120_cs02clkgen ] -max 2.0 [get_ports {MemAdr[*]} ]
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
